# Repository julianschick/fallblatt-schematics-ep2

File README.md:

# Fallblattanzeiger der S-Bahn-Berlin

Platine zur Ansteuerung von 3 Fallblattmodulen (typischerweise Linie, Fahrtziel und Laufweg) mit einem ESP32-Development-Board. Gedacht für Module der *Epoche 2* (siehe [Wikipedia](https://de.wikipedia.org/wiki/Fallblattanzeige)) und ein Eingriff in die Platine der Module ist erforderlich. Der Synchronmotor wird nicht über die Transistorschaltung auf der Platine des Fallblattmoduls gesteuert. Vielmehr wird die Platine so überbrückt, dass der Microcontroller direkten Zugriff auf die Hall-Sensoren hat und über einen eigenen Triac den Synchronmotor direkt steuert.

Zur Stromversorgung wird die Platine an 230 V Netzspannung angeschlossen. Ein großer Trafo, der nicht auf der Platine verbaut wird, sondern über Schraubklemmen angeschlossen werden kann, spannt auf 48V AC herunter. Damit werden die Synchronmotoren der Module betrieben. Ein weiterer Trafo, der auf der Platine montiert wird, spannt auf 9V AC herunter, die gleichgerichtet und mit einem Linearregler auf Logik-Betriebsspannung 3,3V gebracht werden.

## Modifikationen an der Platine des Fallblattmoduls

Der unveränderte Schaltplan der Platine ist als [KiCad-Schaltplan](images/schaltplan-modul/schaltplan-modul.sch) und [PDF](images/schaltplan-modul.pdf) im Repo abgelegt. Soweit möglich, sind Typenbezeichnung der Bauteile mit angegeben, diese sind allerdings mit Google heute nur schwer zu deuten.

Ähnlich wie bei den modernen Varianten (siehe auch [fallblatt-schematics-ep3](https://github.com/julianschick/fallblatt-schematics-ep3)) der Fallblattmodule sind zwei Sensoren verbaut: Ein Sensor, der jedes fallende Blatt zählt (Flap) und einen, der ein bestimmtes Blatt als Nullstellung markiert (Home). Im Gegensatz zu den moderneren Exemplaren sind das allerdings keine Photodioden sondern Hall-Sensoren, an denen ein Magnet vorbeistreicht. Wenn kein Magnet in der Nähe ist, liegt auf dem Ausgang des Sensors VCC an, kommt der Magnet vorbei, so wird der Ausgang sehr sauber (ohne Gewackel) auf GND gezogen. Im Betrieb mit dem Mikrocontroller habe ich allerdings festgestellt, dass die Flap-Sensoren einerseits gerne etwas zu früh triggern, sodass das Blatt noch klemmt, und andererseits beim erneuten Anlaufen manchmal durch die Induktion des in Bewegung gesetzten Magneten noch einmal kurz getriggert werden. Gelöst habe ich beide Probleme auf Softwareseite durch etwas längeres Weiterlaufen und durch Ignorieren des Flap-Sensors direkt nach dem Anlaufen.

Die folgenden Pläne und Bilder zeigen die notwendigen Modifikationen. Einmal wird Pin 5 des Anschlusssteckers von Pin 10 des Anschlusssteckers getrennt, indem ein Widerstand und eine Diode entfernt werden. Außerdem wird Pin 10 direkt mit dem Flap-Hall-Sensor verbunden, durch setzen einer Brücke auf der Platine, wo schon zwei vorbereitete Pads nebeneinander liegen (violette Brücke). Zuletzt wird der Triac entfernt und überbrückt (blaue Brücke).

**Schaltplan mit Modifikationen**

Dieses Bild auch als [PDF](images/schaltplan-modul-modifikationen.pdf) und [SVG](images/schaltplan-modul-modifikationen.svg).

**Modifikationen an der Platine** (blaue und violette Brücke, entfernte Teile)

**Gesamte Platine des Fallblattmoduls / Synchronmotor**

**Polbelegung des Anschlusses**

## Teileliste

* ESP32-Development-Board (es gibt 2 Varianten bei eBay, für diese Platine wird die üblichere mit 15 Pins je Reihe und GND/VCC  nebeneinander, nicht auf gegenüberliegenden Pins benötigt; diese wird oft unter dem Namen _DEVKITV1_ oder _NodeMCU_ verkauft). Das folgende Pinout ist das korrekte:

* Netztrafo 48V (eigentlich 42V) mit Wumms, mind. 200mA pro Modul, der Synchronmotor zieht so viel. Zum Beispiel [der hier](https://www.voelkner.de/products/1011896/TRU-Components-TC-RKT30-2X24-Ringkerntransformator-1-x-230V-2-x-24V-30-VA-625mA.html)
* [Transformator 9V _Block VB 2,0/1/9_](https://www.reichelt.de/printtrafo-2-va-9-v-222-ma-rm-20-mm-ei-30-15-5-109-p27328.html)
* Rundsicherung 1A mit Halter Littelfuse, RM 5mm
* Varistor, mind. 300V, RM 10mm
* [Brückengleichrichter Rund, Wechselstrompins gegenüber, RM 5mm](https://www.reichelt.de/brueckengleichrichter-100-v-1-5-a-b70c1500rund-p181713.html)
* 4 x Schraubklemme 2-polig RM 7,5mm
* [Spannungsregler 3,3V Formfaktor TO-220 _STM LD1117 V33C_](https://www.reichelt.de/ldo-regler-fest-3-3-v-to-220-ld1117-v33c-p200891.html?)
* 3 x Optotriac (Triac mit Optokoppler) MOC3041M, Formfaktor DIP-6
* 3 x Leistungstriac BT136-600, Formfaktor TO-220
* Elektrolytkondensator 470u, RM 5mm
* Elektrolytkondensator 10u, RM 2mm
* Kondensator 100n, RM 2,5mm
* 6 x Widerstand 10K, RM 15mm
* 3 x Widerstand 220, RM 10mm
* 3 x Widerstand 330, RM 10mm
* 2 x Jumpersteckplatz und 2 x Pinheader Female für das ESP32-Board
* 3 x Anschlüsse für die Fallblattmodule (2 x 5 Pole), RM 2,54mm

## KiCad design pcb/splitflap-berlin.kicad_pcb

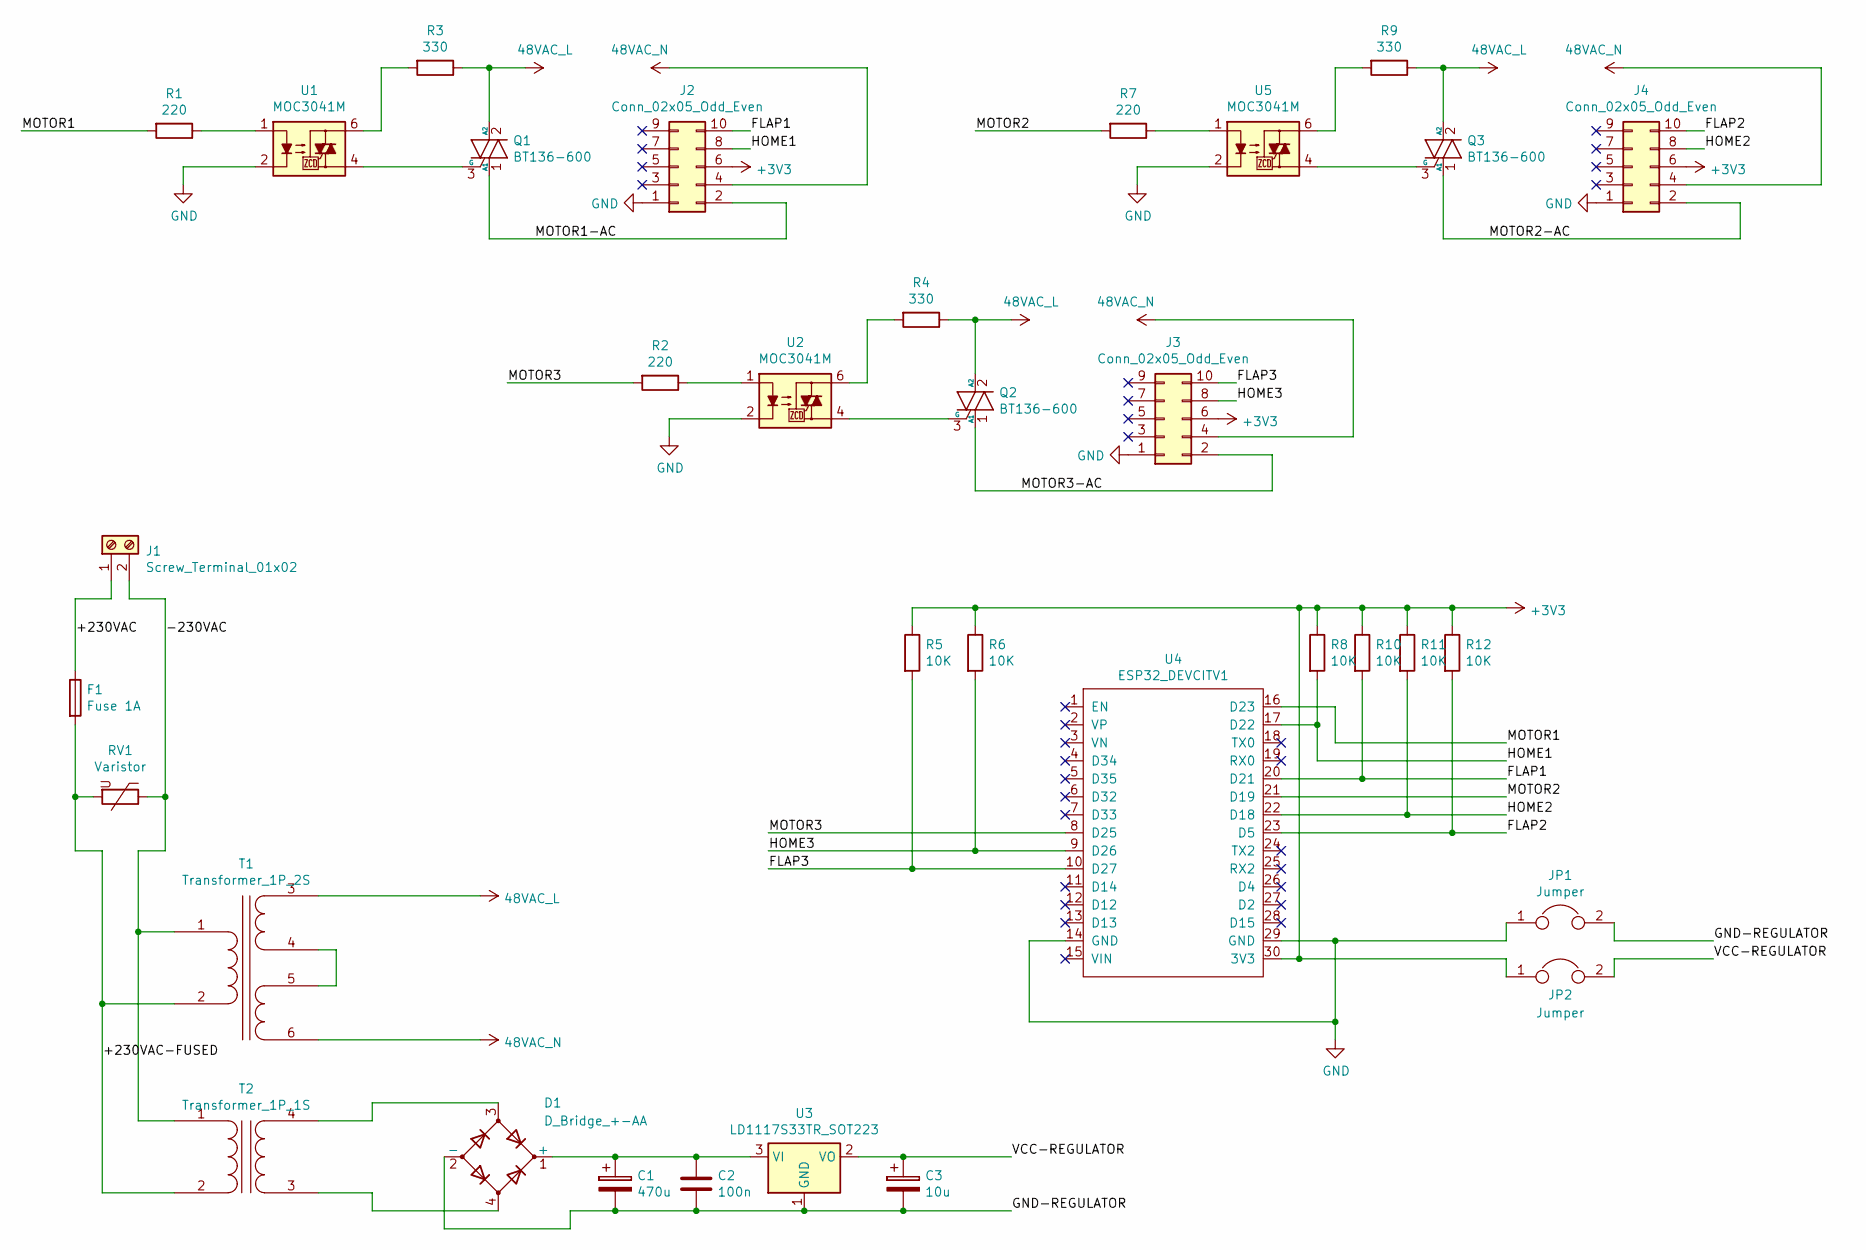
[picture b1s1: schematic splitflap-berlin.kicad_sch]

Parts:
C1: 470u; CP_Radial_D10.0mm_P5.00mm
C2: 100n; C_Disc_D3.0mm_W1.6mm_P2.50mm
C3: 10u; CP_Radial_D4.0mm_P2.00mm
D1: D_Bridge_+-AA; Diode_Bridge_9.5x9.5x10mm_P5.08mm
F1: Fuse 1A; Fuseholder_TR5_Littelfuse_No560_No460
J1: Screw_Terminal_01x02; TerminalBlock_MetzConnect_Type175_RT02702HBLC_1x02_P7.50mm_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
J2, J3, J4: Conn_02x05_Odd_Even; TE_CON_5499922-1_BIGGERHULL
JP1, JP2: Jumper; PinHeader_1x02_P2.54mm_Vertical
Q1, Q2, Q3: BT136-600; TO-220-3_Vertical
R1, R2, R7: 220; R_Axial_DIN0207_L6.3mm_D2.5mm_P10.16mm_Horizontal
R3, R4, R9: 330; R_Axial_DIN0207_L6.3mm_D2.5mm_P10.16mm_Horizontal
R5, R6, R8, R10, R11, R12: 10K; R_Axial_DIN0411_L9.9mm_D3.6mm_P15.24mm_Horizontal
RV1: Varistor; RV_Disc_D21.5mm_W4.3mm_P10mm
T1: Transformer_1P_2S; Transformer_Ext_1P_2S
T2: Transformer_1P_1S; Block_VB_2.0_1_9
U1, U2, U5: MOC3041M; DIP-6_W7.62mm
U3: LD1117S33TR_SOT223; TO-220-3_Vertical
U4: ESP32_DEVCITV1; ESP32_DEVKITV1_16

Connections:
48VAC_L: Q1.2 (A2), Q2.2 (A2), Q3.2 (A2), R3.1, R4.1, R9.1, T1.3 (SA)
48VAC_N: J2.4, J3.4, J4.4, T1.6 (SD)
+3V3: J2.6, J3.6, J4.6, JP2.1, R5.1, R6.1, R8.1, R10.1, R11.1, R12.1, U4.30 (3V3)
/+230VAC: F1.1, J1.1
/+230VAC-FUSED: F1.2, RV1.2, T1.2 (AB), T2.2 (AB)
/-230VAC: J1.2, RV1.1, T1.1 (AA), T2.1 (AA)
/FLAP1: J2.10, R10.2, U4.20 (D21)
/FLAP2: J4.10, R12.2, U4.23 (D5)
/FLAP3: J3.10, R5.2, U4.10 (D27)
/GND-REGULATOR: C1.2, C2.2, C3.2, D1.2 (-), JP1.2, U3.1 (GND)
/HOME1: J2.8, R8.2, U4.17 (D22)
/HOME2: J4.8, R11.2, U4.22 (D18)
/HOME3: J3.8, R6.2, U4.9 (D26)
/MOTOR1: R1.2, U4.16 (D23)
/MOTOR1-AC: J2.2, Q1.1 (A1)
/MOTOR2: R7.2, U4.21 (D19)
/MOTOR2-AC: J4.2, Q3.1 (A1)
/MOTOR3: R2.2, U4.8 (D25)
/MOTOR3-AC: J3.2, Q2.1 (A1)
/VCC-REGULATOR: C3.1, JP2.2, U3.2 (VO)
GND: J2.1, J3.1, J4.1, JP1.1, U1.2, U2.2, U4.14 (GND), U4.29 (GND), U5.2
unnamed: C1.1, C2.1, D1.1 (+), U3.3 (VI)
unnamed: D1.3, T2.4 (SB)
unnamed: D1.4, T2.3 (SA)
unnamed: Q1.3 (G), U1.4
unnamed: Q2.3 (G), U2.4
unnamed: Q3.3 (G), U5.4
unnamed: R1.1, U1.1
unnamed: R2.1, U2.1
unnamed: R3.2, U1.6
unnamed: R4.2, U2.6
unnamed: R7.1, U5.1
unnamed: R9.2, U5.6
unnamed: T1.4 (SB), T1.5 (SC)

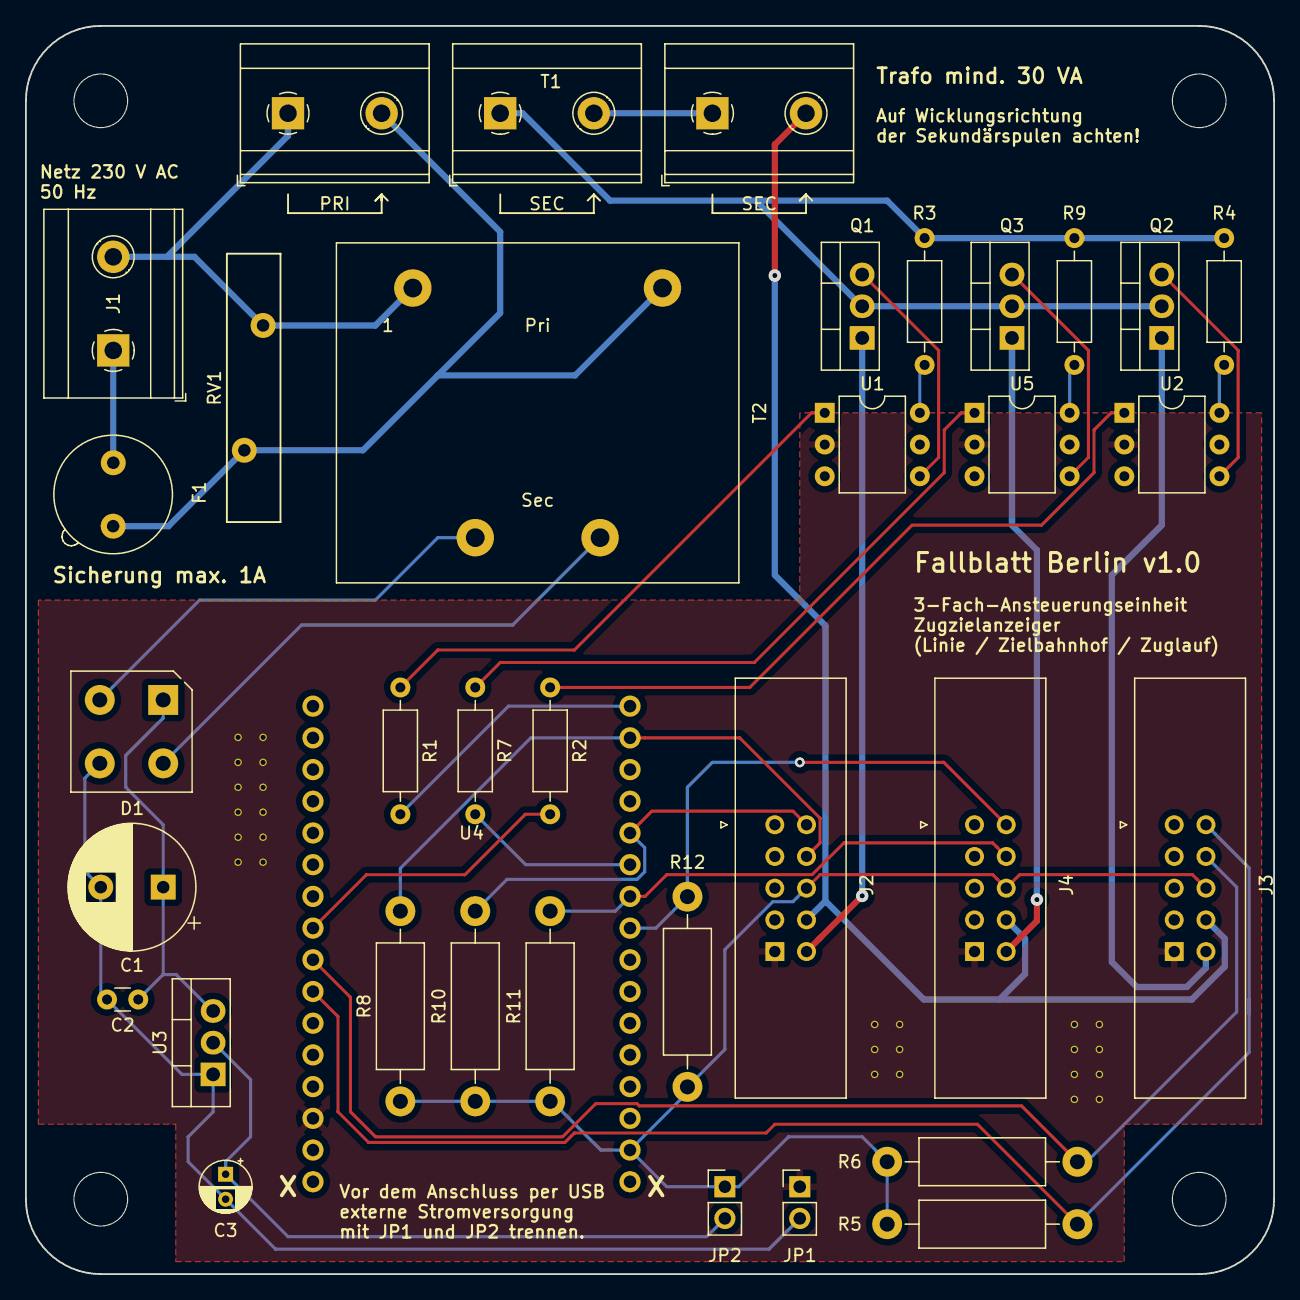
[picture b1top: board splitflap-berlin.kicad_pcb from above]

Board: 2 copper layers, 100.0 x 100.0 mm, 34 parts (0 on the bottom side), 34 nets.

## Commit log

2019-10-24 initial
2020-04-05 images added
2020-04-05 demo images added
2020-04-05 datasheets added
2024-11-16 opened with newer kicad-version
